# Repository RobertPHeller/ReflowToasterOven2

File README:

This project is based on the Instructables "Hack a Toaster Oven for Reflow
Soldering" by frank26080115 at
https://www.instructables.com/id/Hack-a-Toaster-Oven-for-Reflow-Soldering/

Notable differences:

1) It uses an Adafruit Feather M0 Expressas the processing element and all of
the electronics (except the display, pushbuttons, buzzer, and relay) are
mounted on an cut down BusBoard Prototype Systems BR1 solderable breadboard --
all of the components are through-hole components.

There is a KiCAD project here. It includes a "four layer" board. Actually I
have no intention of creating a "four layer" PCB. I intend to build this on
aBusBoard Prototype Systems BR1 solderable breadboard. The PCB I "designed"
with KiCAD is a mock up for the BR1 solderable breadboard. The green layer
represent the wiring already on the BR1 solderable breadboard, and includes
the bus strips. The red, blue and white "layers" represent the added wiring.
The board also provides the component placement. For those people without
KiCAD installed, I have included a PDF of the schematic in the file
ReflowToasterOven2.pdf and a SVG file of the board showing the layout.

2) Everything is mounted in a pair of plastic boxes and instead of "hacking"
an extension code, an AC power entry module and a pair of AC Receptacles are
used.

There are three files related to the mechanical construction:

ReflowToasterOven-mech2.tcl
ReflowToasterOven-mech2.gcad
ReflowToasterOven-mech2.dxf

ReflowToasterOven-mech2.tcl is a Tcl program that generates the 
ReflowToasterOven-mech2.gcad file, which is the input for the GCAD3D program.  
The ReflowToasterOven-mech2.dxf is a DXF file, that can be imported to any 3D 
cad program.

3) An Adafruit 1.8" *Color* TFT LCD SPI display is used, using Adafruit's 
graphics library.

4) The software is a "standard" Arduino project.

And the code lives in the ReflowToasterOven2 subdirectory. It compiles
successfully and just fits in the Uno's flash memory and only 1/2 of the SRAM
is used by static variables, leaving just under 1K for dynamic variables.

You will need to install the Adafruit ST7735 and Adafruit_GFX libraries from 
Adafruit's GitHub repo.  You will also need the MsTimer2 library 
(http://www.pjrc.com/teensy/td_libs_MsTimer2.html).

*Most* of the code is copied from the original program by frank26080115.  I 
modified things to use C++ classes and adapted to use the Arduino I/O 
libraries, the Adafruit ST7735-based TFT display and the MsTimer2 library.

I have not built or tested it yet.

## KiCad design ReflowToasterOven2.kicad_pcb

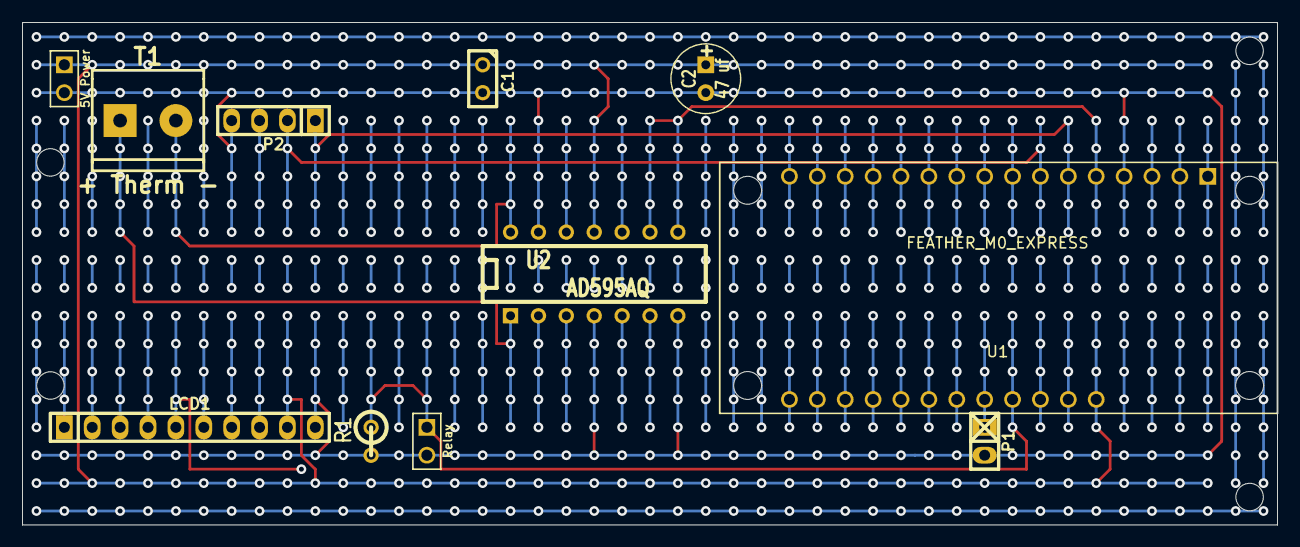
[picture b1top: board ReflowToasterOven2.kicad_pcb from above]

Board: 4 copper layers, 114.3 x 45.8 mm, 15 parts (0 on the bottom side), 17 nets.

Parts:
C1: .1 uf; C1
C2: 47 uf; C1V7
LCD1: 160X128_TFT_DISPLAY; pin_strip_10
MH: MountingHole_2-5mm_RevA_Date21Jun2010
MH#2, MH#3, MH#4: MountingHole_2-5mm_RevA_Date21Jun2010
P1: Buzzer; pin_strip_2
P2: Switches; pin_strip_4
R1: 10K Ohms; R1
T1: + Therm -; mors_2p
T2: 5V Power; ScrewTerm2.54-2
T3: Relay; ScrewTerm2.54-2
U1: FEATHER_M0_EXPRESS; AdafruitFeather
U2: AD595AQ; DIP-14__300

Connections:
+5V: C1.1, C2.1, LCD1.9, T2.1, U1.28, U2.11
/Buzzer: P1.1, U1.24
/D/C: LCD1.7, U1.22
/Lite: LCD1.1, U1.19
/MISO: LCD1.2, U1.13
/MOSI: LCD1.4, U1.12
/Relay Control: R1.1, T3.1, U1.25
/SCK: LCD1.3, U1.11
/Switch 1: P2.1, U1.6
/Switch 2: P2.2, U1.7
/Switch 3: P2.3, U1.8
/TFT_CS: LCD1.5, U1.20
/TFT_RST: LCD1.8, U1.23
/Temp Out: U1.5, U2.8, U2.9
GND: C1.2, C2.2, LCD1.10, P1.2, P2.4, R1.2, T2.2, T3.2, U1.4, U2.4, U2.7, U2.13
unnamed: T1.1, U2.1
unnamed: T1.2, U2.14

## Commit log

2018-06-26 Initial Release
2018-06-26 Label Update
2018-06-26 Add file system menu.
2018-06-26 Fix file name typo
2018-06-26 Reorder filesystem menu
2018-06-27 Add a readme
2018-07-06 Updates to mechanicals
2018-08-10 Ready for the actual toaster oven and final testing and calibration
2018-08-21 Update buildTC.sh for arm host (Raspi)
2018-08-25 Updates to ToasterConsole.tcl -- add CLI options for all Input and Output filenames.
2019-11-06 Turn off demo mode.
2019-11-06 Change out of DEMO mode
2019-11-06 restore reflowtoasteroven.h
2019-11-06 reflowtoasteroven.h
2020-08-26 Add Fritzing and FreeCAD files.
2020-08-27 Add Button Board.
